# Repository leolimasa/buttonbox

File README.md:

# buttonbox

A circuit board for Arduino nano with HID buttons for flight simulators.

2x3 rotary encoders in a circuit board.

## Features

* Heading (heading hold)
* Altitude (FLC)
* Vertical speed (VS)
* Speed (IAS hold)
* Altimeter
* COM radio

## Future

The goal is to have a 2x4 rotary encoders board with an extra 8 buttons. 

The amount of switches is limited by the number of pins on the Arduino nano. An alternative to increase that without using a multiplexer is to wire the switches in a matrix.

Each rotary takes 3 buttons. With 8 rotaries, that's 24 buttons.

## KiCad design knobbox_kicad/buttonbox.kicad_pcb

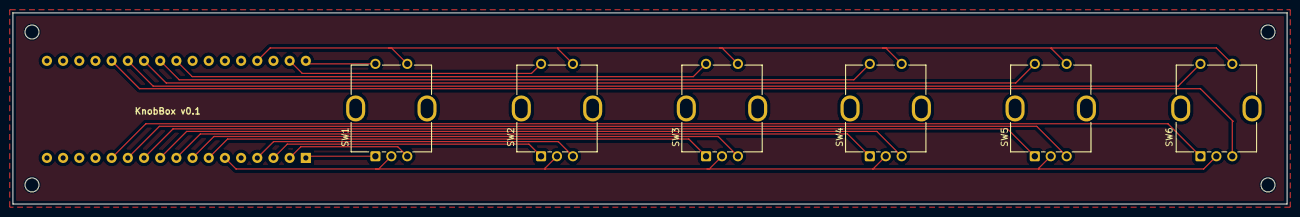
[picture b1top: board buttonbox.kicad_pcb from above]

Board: 2 copper layers, 200.0 x 30.0 mm, 11 parts (1 on the bottom side), 20 nets.

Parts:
Arduino: Arduino_Micro
H1, H2, H3, H4: MountingHole; MountingHole_2.2mm_M2
SW1, SW2, SW3, SW4, SW5, SW6: RotaryEncoder_Switch; RotaryEncoder_Bourns_Vertical_PEC12R-3x17F-Sxxxx

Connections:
D0: Arduino.4 (D0/RX), SW2.B
D1: Arduino.3 (D1/TX), SW2.A
D2: Arduino.7 (D2/SDA), SW3.A
D3: Arduino.8 (~D3/SCL), SW3.B
D4: Arduino.9 (D4/A6), SW4.A
D5: Arduino.10 (~D5), SW4.B
D6: Arduino.11 (~D6/A7), SW5.A
D7: Arduino.12 (D7), SW5.B
D8: Arduino.13 (D8/A8), SW6.A
D14: Arduino.33 (D14), SW2.S1
D15: Arduino.34 (D15), SW1.S1
D16: Arduino.1 (D16), SW1.A
D17: Arduino.2 (D17), SW1.B
D19: Arduino.22 (A1/D19), SW6.B
D20: Arduino.23 (A2/D20), SW6.S1
D21: Arduino.24 (A3/D21), SW5.S1
D22: Arduino.25 (A4/D22), SW4.S1
D23: Arduino.26 (A5/D23), SW3.S1
GND: Arduino.6 (GND), SW1.C, SW2.C, SW3.C, SW4.C, SW5.C, SW6.C
GND2: Arduino.31 (GND), SW1.S2, SW2.S2, SW3.S2, SW4.S2, SW5.S2, SW6.S2

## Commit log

2024-11-03 started on arduino code
2024-11-03 knob works
2024-11-04 button works
2024-11-04 added joystick support
2024-11-04 rotary joystick button hold
2024-11-10 kicad board and preparing for protobuf
2024-11-10 removed old kicad files
2024-11-12 renamed main folders
2024-11-12 serial driver works with protobuf
